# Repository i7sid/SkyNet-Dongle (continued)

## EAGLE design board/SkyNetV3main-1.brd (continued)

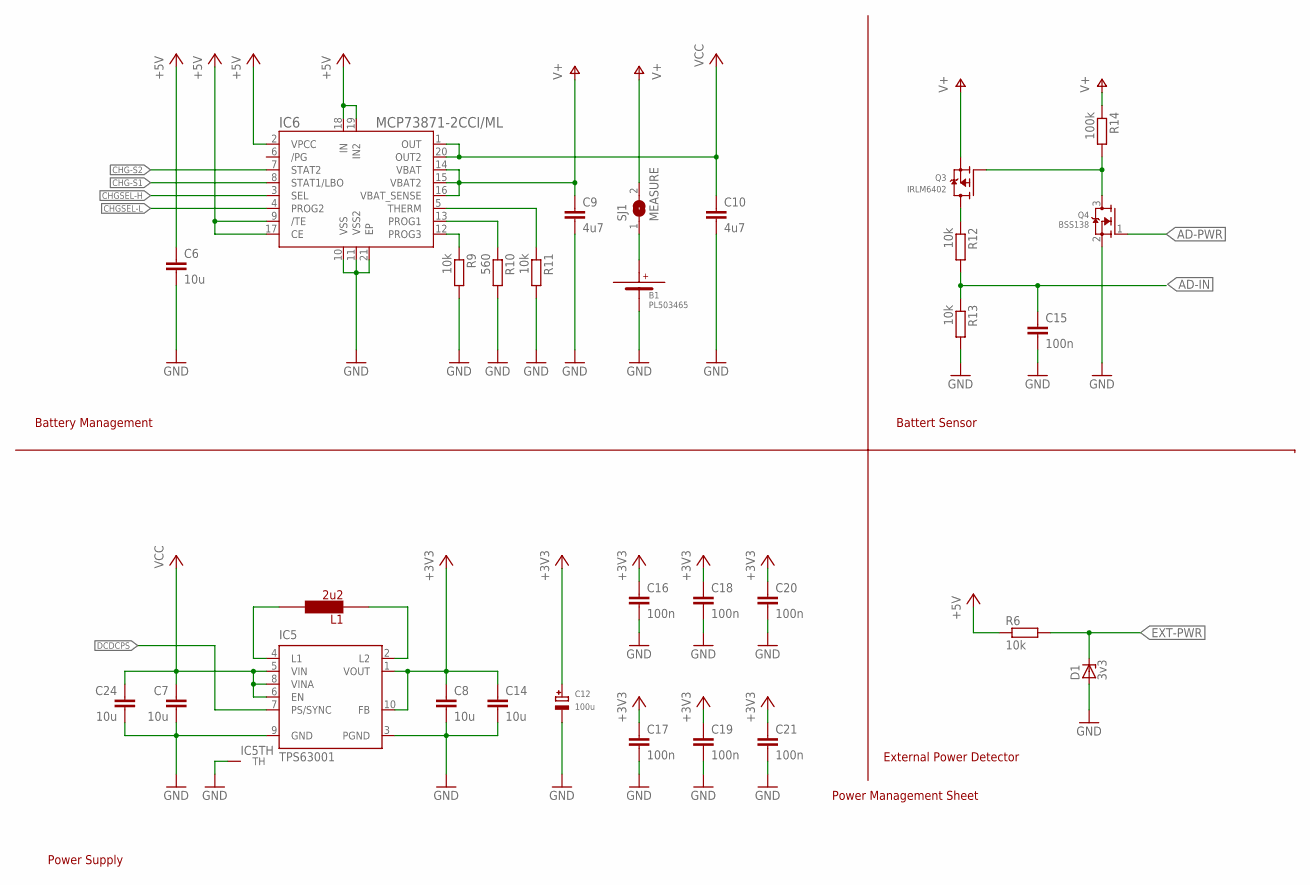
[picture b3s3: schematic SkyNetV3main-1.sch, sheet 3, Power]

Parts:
B1: PL503465
C6, C7, C8, C14, C24: 10u; C1206K
C9, C10: 4u7; C1206K
C12: 100u; EIA6032-28/C-W
C15, C16, C17, C18, C19, C20, C21: 100n; C0603
D1: 3v3; SOT23
IC5: TPS63001; DRC-S-PVSON-N10
IC6: MCP73871-2CCI/ML; QFN20-4X4
L1: 2u2; LPS4012
Q3: IRLM6402; SOT23-WIDE
Q4: BSS138; SOT23-WIDE
R6, R9, R11, R12, R13: 10k; R0603
R10: 560; R0603
R14: 100k; R0603
SJ1: MEASURE; SJ

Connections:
+3V3: C8.1, C12.+, C14.1, C16.1, C17.1, C18.1, C19.1, C20.1, C21.1, IC5.1 (VOUT), IC5.10 (FB); also elsewhere on the board
+5V: C6.1, IC6.2 (VPCC), IC6.9 (/TE), IC6.17 (CE), IC6.18 (IN), IC6.19 (IN2), R6.1; also elsewhere on the board
AD-IN: C15.1, R12.2, R13.1; also elsewhere on the board
AD-PWR: Q4.1 (G); also elsewhere on the board
AD-PWR-FET: Q3.1 (G), Q4.3 (D), R14.2
AD-PWR-FET2: Q3.3 (D), R12.1
CHG-S1: IC6.8 (STAT1/LBO); also elsewhere on the board
CHG-S2: IC6.7 (STAT2); also elsewhere on the board
CHGSEL-H: IC6.3 (SEL); also elsewhere on the board
CHGSEL-L: IC6.4 (PROG2); also elsewhere on the board
DCDCPS: IC5.7 (PS/SYNC); also elsewhere on the board
EXT-PWR: D1.3 (C), R6.2; also elsewhere on the board
GND: B1.P-, C6.2, C7.2, C8.2, C9.2, C10.2, C12.-, C14.2, C15.2, C16.2, C17.2, C18.2, C19.2, C20.2, C21.2, C24.2, D1.1 (A), IC5.3 (PGND), IC5.9 (GND), IC5.TH, IC6.10 (VSS), IC6.11 (VSS2), IC6.21 (EP), Q4.2 (S), R9.2, R10.2, R11.2, R13.2; also elsewhere on the board
L1: IC5.4 (L1), L1.1
L2: IC5.2 (L2), L1.2
unnamed: B1.P+, SJ1.1
PROG1: IC6.13 (PROG1), R10.1
PROG3: IC6.12 (PROG3), R9.1
THERM: IC6.5 (THERM), R11.1
V+: C9.1, IC6.14 (VBAT), IC6.15 (VBAT2), IC6.16 (VBAT_SENSE), Q3.2 (S), R14.1, SJ1.2
VCC: C7.1, C10.1, C24.1, IC5.5 (VIN), IC5.6 (EN), IC5.8 (VINA), IC6.1 (OUT), IC6.20 (OUT2)

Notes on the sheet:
Battery Management
Power Supply
External Power Detector
Battert Sensor
Power Management Sheet

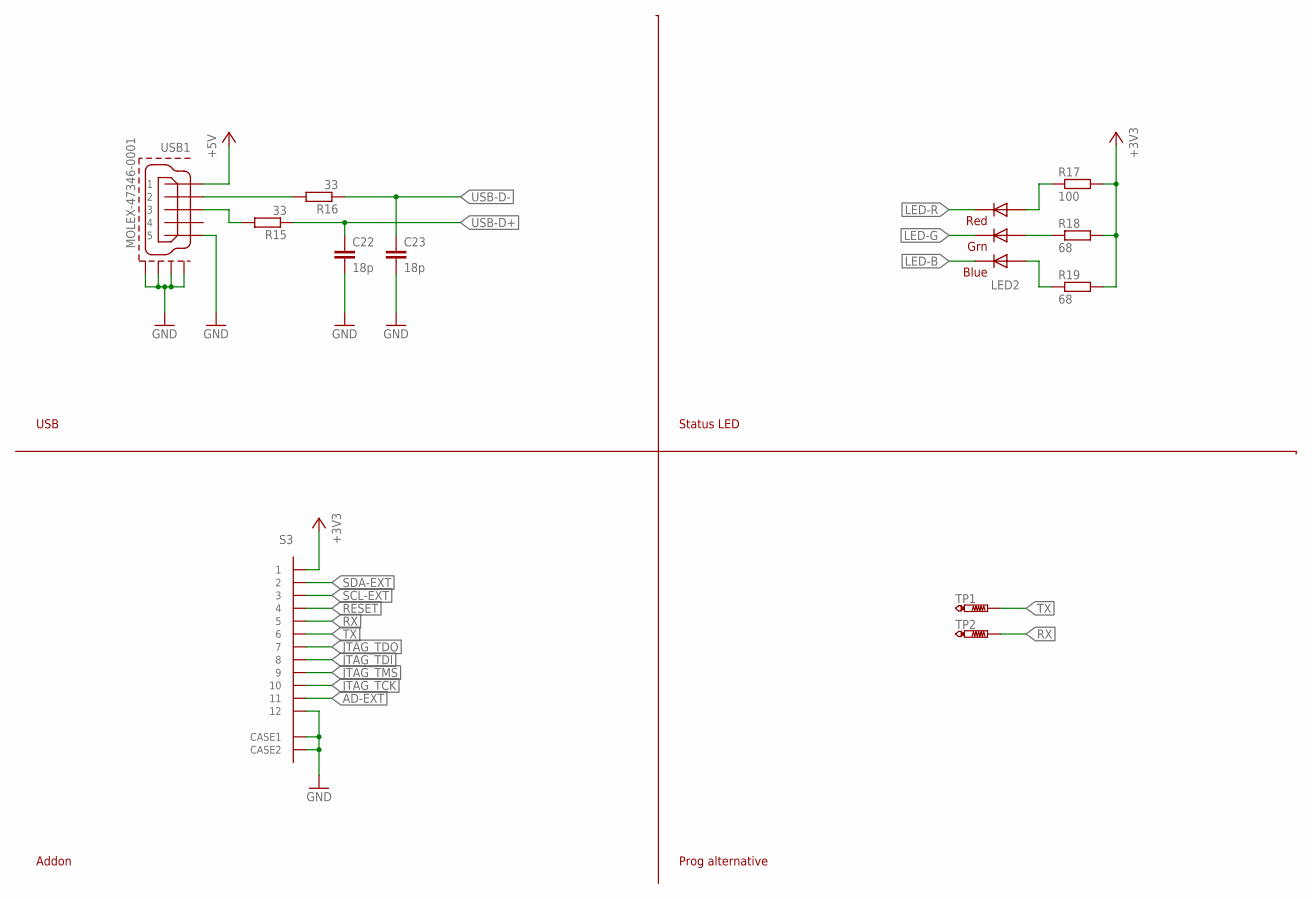
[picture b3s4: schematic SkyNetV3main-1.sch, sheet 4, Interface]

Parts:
C22, C23: 18p; C0603
LED2: RGBLED5050
R15, R16: 33; R0603
R17: 100; R0603
R18, R19: 68; R0603
S3: MOLEX-52892-1233
TP1, TP2: PTR1B1,27; B1,27
USB1: MOLEX-47346-0001; MOLEX-47364-0001

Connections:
+3V3: R17.2, R18.2, R19.2, S3.P$1 (1); also elsewhere on the board
+5V: USB1.1; also elsewhere on the board
AD-EXT: S3.P$11 (11); also elsewhere on the board
GND: C22.2, C23.2, S3.P$12 (12), S3.P$GND1 (CASE1), S3.P$GND2 (CASE2), USB1.5, USB1.GND1, USB1.GND2, USB1.GND3, USB1.GND4; also elsewhere on the board
JTAG_TCK: S3.P$10 (10); also elsewhere on the board
JTAG_TDI: S3.P$8 (8); also elsewhere on the board
JTAG_TDO: S3.P$7 (7); also elsewhere on the board
JTAG_TMS: S3.P$9 (9); also elsewhere on the board
LED-B: LED2.4 (BLUE_C); also elsewhere on the board
LED-B-R: LED2.3 (BLUE_A), R19.1
LED-G: LED2.6 (GREEN_C); also elsewhere on the board
LED-G-R: LED2.1 (GREEN_A), R18.1
LED-R: LED2.5 (RED_C); also elsewhere on the board
LED-R-R: LED2.2 (RED_A), R17.1
RESET: S3.P$4 (4); also elsewhere on the board
RX: S3.P$5 (5), TP2.TP; also elsewhere on the board
SCL-EXT: S3.P$3 (3); also elsewhere on the board
SDA-EXT: S3.P$2 (2); also elsewhere on the board
TX: S3.P$6 (6), TP1.TP; also elsewhere on the board
USB-CABLE-D+: R15.2, USB1.3; also elsewhere on the board
USB-CABLE-D-: R16.2, USB1.2
USB-D+: C22.1, R15.1; also elsewhere on the board
USB-D-: C23.1, R16.1; also elsewhere on the board

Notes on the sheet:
USB
Status LED
Prog alternative
Addon

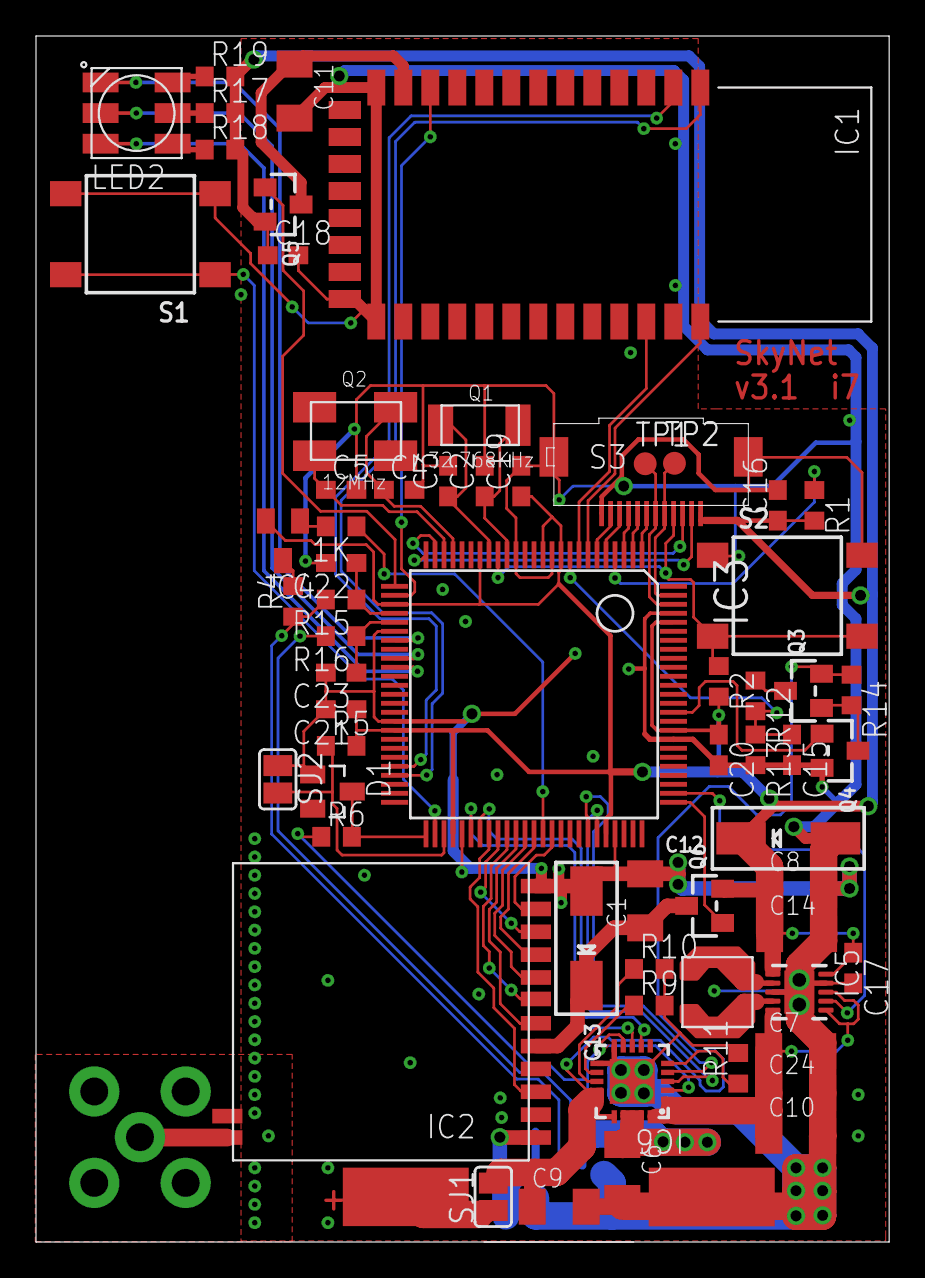
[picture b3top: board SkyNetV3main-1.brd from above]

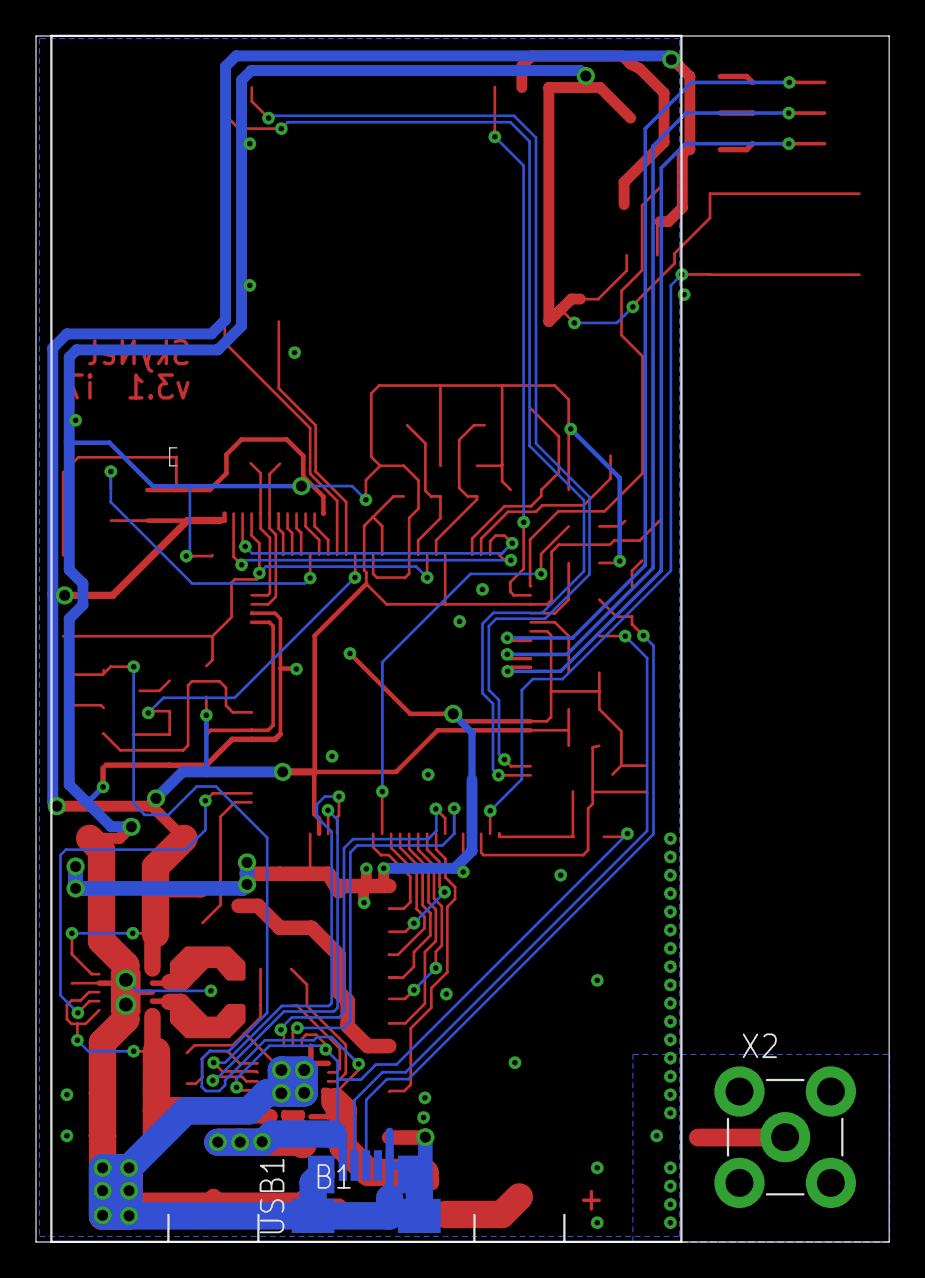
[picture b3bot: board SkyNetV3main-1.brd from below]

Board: 2 copper layers, 47.4 x 67.0 mm, 66 parts (3 on the bottom side), 68 nets.

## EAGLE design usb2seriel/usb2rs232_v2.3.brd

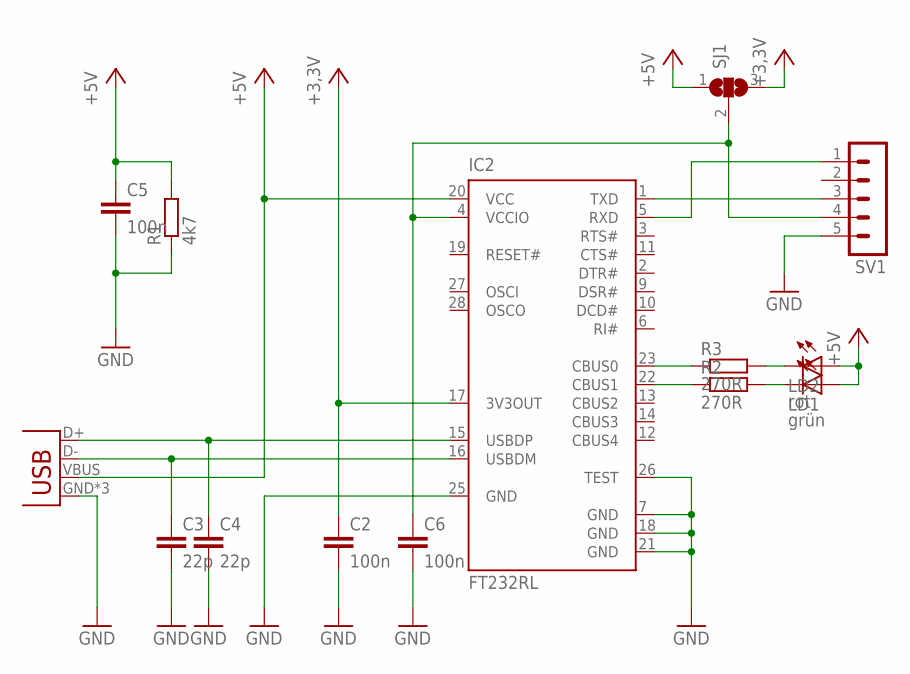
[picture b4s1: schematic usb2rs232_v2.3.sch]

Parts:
C2, C5, C6: 100n; C0603
C3, C4: 22p; C0603
IC2: FT232RL; SSOP28
JP2: USB-MICROB
LD1: grün; CHIP-LED0603
LD2: rot; CHIP-LED0603
R1: 4k7; R0603
R2, R3: 270R; R0603
SJ1: SJ2W; SJ_2
SV1: MA05-1

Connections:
+3,3V: C2.1, IC2.17 (3V3OUT), SJ1.3
+5V: C5.1, IC2.20 (VCC), JP2.VBUS, LD1.A, LD2.A, R1.2, SJ1.1
GND: C2.2, C3.2, C4.2, C5.2, C6.2, IC2.7 (GND), IC2.18 (GND), IC2.21 (GND), IC2.25 (GND), IC2.26 (TEST), JP2.GND, JP2.MT1 (GND), JP2.MT2 (GND), R1.1, SV1.5
unnamed: IC2.23 (CBUS0), R3.1
unnamed: IC2.22 (CBUS1), R2.1
unnamed: C4.1, IC2.15 (USBDP), JP2.D+
unnamed: C3.1, IC2.16 (USBDM), JP2.D-
unnamed: C6.1, IC2.4 (VCCIO), SJ1.2, SV1.4
unnamed: LD1.C, R2.2
unnamed: LD2.C, R3.2
unnamed: IC2.5 (RXD), SV1.1
unnamed: IC2.1 (TXD), SV1.3

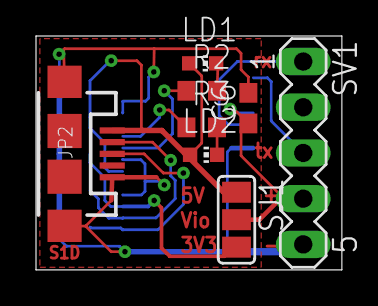
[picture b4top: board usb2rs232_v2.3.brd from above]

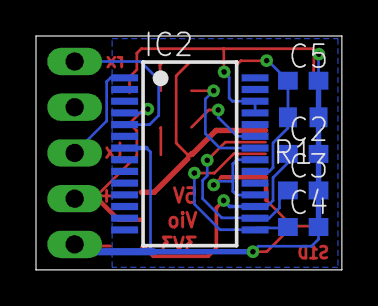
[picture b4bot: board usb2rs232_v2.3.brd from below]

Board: 2 copper layers, 17.0 x 13.0 mm, 14 parts (6 on the bottom side), 12 nets.

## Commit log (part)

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2014-05-26 basic directory structure
2014-05-26 initial commit (schematics)
    + first version of README.md
    + first sketch of schematics
    TODO on schematics:
    + power supply, charging and battery interfacing
2014-06-10 further schematics development; layout started
2014-06-10 further layout, got stuck somewhere...
2014-06-10 board further
2014-06-10 added ground planes
2014-06-11 layout optimizations, tStop corrected
2014-06-13 new layout
2014-06-15 another layout try, looks much better now
2014-06-16 layout improvements
2014-06-16 corrected USB connector in layout+schematics
2014-06-16 usb2seriel adapter for debugging and firmware uploading
2014-06-17 corrected some distance problems and missing VALUEs
2014-07-15 initial firmware commit
    no "read to run" version
2014-07-31 further firmware
2014-08-15 some further firmware work
    + RF working
    + bluetooth basically working
    TODO:
    - switch on / off
    - ...
2014-08-15 bluetooth pairing possible
2014-08-17 sleep basically works; basic RF transceiving works
2014-08-18 layout & schematic fixes
    + layout: better ground flow
    + layout: more space for single parts
    + layout: marked GND on battery
    + layout: marked pinouts
    + schematics: fixed USB-connect->USB-plus connection
2014-08-18 prepared firmware for flashing via USB
2014-09-07 firmware cleanups and TODOs, USB bootloader added
    + added 2 projects from Code Red Technologies to support USB bootloading
2014-09-16 variable packets with 4096B - that must be enough!
2014-09-16 some cleanups
2014-09-21 bluetooth is_connected stuff, event handling for packets
2014-10-11 board: connected PS/SYNC of buck boost converter
2014-10-14 Connected PS/SYNC of DC/DC
2014-10-14 some minor firmware changes
2014-10-14 minor firmware things
2014-11-07 Schematic revised. TODO Radio remains
2014-11-13 Schematic revised
2014-11-14 psu done
2014-11-15 firmware: Check "is BT connected" via GPIO
    behaviour was: enable AT mode, ask, disable AT mode
    (was very unstable!)
2014-11-17 cpu moved
2014-11-21 pre-molex-connector
2014-11-24 routing done
2014-11-24 cleanup after routing
2014-11-27 new connector
2014-12-01 case added
2015-01-13 added support for usb pocket
2015-01-13 position adjustments
2015-01-13 added todos
2015-01-16 first try of breakout board
2015-01-20 breakout board now one-sided
2015-01-22 adapted firmware to new board
2015-01-22 net names corrected for led
2015-01-29 next iteration
2015-01-29 reduzed button radius
2015-02-02 breakout board added header
2015-02-02 slightly adjusted to new board, no bootloader
    currently the memory map is configured such that
    no usb bootloader should be installed
    (for development and testing purposes)
2015-02-02 added doc (removed vom gitignore)
2015-02-07 some debugging stuff added (testing current consumption)
2015-02-09 added mounting holes
2015-03-04 debug stuff added
2015-04-01 mini dongle added
2015-04-07 improved placement
2015-04-09 added dcdc
2015-04-14 almost done
2015-04-15 mitten drin
2015-04-16 done
2015-04-27 first version of basestation firmware
2015-04-27 new files for basestation firmware
2015-04-27 fixed winddirection overflow
2015-04-29 implemented mutex and synchronisation of adc access
2015-05-07 using buffered event queue now
2015-05-07 fixed gpio interrupt
2015-06-11 bugfixing, cleanup, gpiointerrupt, doku, gpsmodul
2015-06-11 deleted old files
2015-06-24 ported to board version 3.1
2015-07-10 Some funktionalities of the Communikation Protokoll and bug fixing
2015-07-10 some more fixing
2015-07-26 more features of communication protokoll
2015-10-23 first successfull usb cdc test; LED: adjusted to single
2015-10-25 adjusted gitignore to ignore eclipse .metadata dir
2015-10-25 usb cdc driver interface, event added
2015-10-25 forgot return statement
2015-11-09 adjusted led
2015-11-10 basestation rewrite started (removed old completely)
    + usb message
    + usb host application started
2015-11-10 updated source documentation
2015-11-11 usb messages work now from uC to Host
2015-11-11 usb works in both directions; better events
2015-11-13 usb host improved, minor cleanups
2015-11-13 cleaned up, added debug scenarios
2015-11-13 further cleanups (code: warnings, more bluetooth stuff)
2015-11-17 forgotten free added; skynet<->usb bidirectional
2015-11-18 usb improved
2015-12-03 added reference to test repo for bootloader
2015-12-04 bootloader working again
2015-12-04 added debug config for version with bootloader
    + removed old launch configurations
2015-12-04 host application improved; some debug adjustments
2015-12-04 minor optical improvement in host
2015-12-04 again minor optical in host
2015-12-04 host: added method to reset device
2015-12-04 bootloader added (no git submodules; including binary build)
2015-12-04 adjusted README to new bootloader
2015-12-05 some compass tests
2015-12-06 windvane works
2015-12-06 wind cups added
2015-12-06 some code cleanups
2015-12-06 updated doxygen build
2016-01-06 gps basically works
2016-01-29 compass works basically
2016-01-29 compass: cleaned up code
2016-02-01 bootloader: generate checksum; load user prog only if checksum valid
2016-02-02 first data structures for mac
2016-02-04 small fix, test added
2016-02-05 crc integrated
2016-02-05 adjusted some mac stuff to board
2016-02-05 added source to crc16 function
2016-02-08 added bash script to create tap device
2016-03-15 mac further
2016-03-15 mac packet assembly further
2016-04-05 before lpcxpresso update
2016-04-06 after lpcxpresso ide update
2016-04-06 some cleanup
2016-04-06 minor cleanups
2016-04-06 fixed usb not reconnecting, minor cleanup
2016-04-06 small fixes/workarounds, TAP testing
2016-04-08 mac data frame: unpack method; host: some stuff
2016-04-08 host: tap->usb further
2016-04-08 changed host to work an mac layer
2016-04-08 changed usb-host to makefile project, no need for eclipse/LPCXpresso
2016-04-08 removed binary
2016-04-08 host: error handling improved
2016-04-08 improved cdc handling: larger packets possible (via hack)
2016-04-08 removed debug return in host
2016-04-08 fixed some host issues
2016-04-09 fixed bug with fstream in host app
2016-04-09 added sysctl call to setup-tap-script
    avoid problems with reverse packet filter
2016-04-09 host: improved setup script
2016-04-12 host debug: dest mac addr always broadcast
2016-04-12 host: some further debug
2016-04-12 host: further debug (tap: no packet info)
2016-04-12 transmit ether_type in src_address
2016-04-12 fixed bug in mac addresses
2016-04-12 arp works via ether_type hack, so do not disable on setup
2016-04-13 host debug further
2016-04-13 dbg host: added some bytes at end that may be destroyed
2016-04-13 dbg host: try to correct bug in previous workaround
2016-04-13 host: decreased overhead
2016-04-13 removed backup file that was added by chance
2016-04-13 some firmware changes for cdc and tunneling
2016-04-14 todo marker
2016-04-14 improved usb timing
2016-04-14 watchdog added
2016-04-14 some adjustments for base
2016-04-19 nv storage, etc.
2016-04-19 firmware binary for demo added
2016-04-19 usb timing parameter adjusted
2016-04-19 host: removed debug outputs
2016-04-19 some host debug
2016-04-19 some debug for large packets
2016-04-19 debug further
2016-04-19 some timing tests on host side
2016-04-19 bug with queue fixed
2016-04-20 host debug
2016-04-20 host: reopen tty automatically
2016-04-20 host: bug in memory allocation fixed
2016-04-20 some improvements in usb cdc handling
2016-04-20 added mtu to setup-tap.sh
2016-04-28 first try for extheaders in mac
2016-04-28 fixed malloc size bug in extheader unpack
2016-04-28 base station basically sends
2016-04-29 dongle cmd added, some further extheaders, sync for events
2016-04-30 compass calibration works
2016-05-01 some refactoring of host
2016-05-01 some cleanup, ncurses added to makefile
2016-05-01 ncurses further
2016-05-01 menu basically works
2016-05-02 some gui working
2016-05-02 nearly no linux/* headers
2016-05-02 added compile time option to disable tap
2016-05-02 tried to remove further ethernet dependencies for NO_TAP
2016-05-03 some mysql stuff for host app
2016-05-03 main.c for basestation fix
2016-05-03 first web models (using doctrine2)
2016-05-04 removed bug in radio TX
    Hooray!
    + many gui features...
2016-05-06 tests for base station
2016-05-06 NO_DB for host app
2016-05-06 NO_DB fix further
2016-05-06 NO_TAP fixed
2016-05-06 applied si4463 patch, minor fixes
2016-05-07 found problem (was crc) + some debug stuff
2016-05-07 stil some problems
2016-05-07 possible workaround for weird packet handler bug
    clear tx fifo after TX by manually writing 0x0
2016-05-07 small radio improvement
2016-05-07 windspeed measurement improved
2016-05-07 small host fixes
2016-05-07 firmware: added -Werror, warnings=errors
    + adjusted code to compile
2016-05-07 adjusted radio_cts_timeout
2016-05-07 better seed for PRNG
2016-05-07 base: generate random mac if none set
2016-05-07 changed wind dir to compensated
2016-05-07 CSMA: CCA adjusted
2016-05-10 gui compiling bug fixed
    + some preparations for resizable GUI
2016-05-10 send-ack-method added; volatile configuration
2016-05-11 added compile configurations for base; some code cleanup
2016-05-11 minor code cleanup; added broadcast reception
2016-05-11 write sensor data to text file (for sure)
2016-05-11 fixed bug in wind speed: got never null
2016-05-12 radio pa level config msg; fixed host compile bug
2016-05-12 base: fixed bug in auto-mac routine
2016-05-14 php: simple script for db output added
2016-05-17 fixed missing free() in firmware
2016-05-17 some gui improvements; added payload RX terminating null byte
2016-05-17 db model: changed entity value to string
2016-05-17 php export: positions and mean of positions
2016-05-17 adjusted .gitignore of usb-host
2016-05-19 host: start/stop measurement
2016-05-19 compatibility for cygwin improved
2016-05-19 fix prev commit
2016-06-10 some (preperation) tries for ACKs; SEND EACH PACKET 3 TIMES
2016-06-16 fixed bug in compass calibration; send winddir raw
2016-06-16 gui: added function to stop calibration manually
2016-06-21 rf power test
2016-06-21 basic data structure for measurement
2016-06-21 host: better incoming data representation and presentation
2016-06-21 added better output framework, basic station output json
2016-06-22 basic wind drawing in map (QGIS via GeoJSON)
2016-06-22 added new csv output module
2016-06-23 DB as new output handler
2016-06-23 host: averaging (intuitive not-optimized algorithm)
2016-06-24 added basic multihop functionality
2016-06-24 malloc and free counter output
2016-06-30 fixed some retransmission issues; added basic multihop (ttl=2)
2016-07-02 removed debug (lead to bug)
2016-07-07 test lower bitrate
2016-07-09 added compatibility for windows host
2016-07-13 fixed little bug in windspeed
2016-07-13 host: raw dir to csv output
2016-07-13 windspeed: added alternate speed measurement
2016-07-18 added usb type for simple range tests
2016-08-01 UART between base and feather works
2016-08-03 base: dfx further
2016-08-03 base with feather: works basically
    problem: multiple received packets are recognized multiple times
2016-08-05 send base to feather even if gps fix missing
2016-08-09 history in basestation
2016-08-11 base: basic CCA, watchdog
2016-09-05 feather: fixed mac bug, mac in library; multihop
2016-09-05 ide internal stuff
2016-09-05 host: first try to implement updraft detection
2016-09-05 host Makefile: TODO target
2016-09-07 host: thermal further
2016-09-07 added fifo output
2016-09-07 host: activated fifo in main
2016-09-08 fixed some fifo issues, fixed which data is transmitted
2016-09-20 environment for analysis added
2016-09-21 rangetest: rx works, some further adjustments
2016-09-22 udev rules file added
2016-09-22 fixed WDT bug in rangetest TX feather
2016-09-23 added rangetest data from 2016/09/09
2016-10-13 webapp added
2016-10-21 model before vecetor based
2016-10-21 model changed to use vector updrafts
2016-10-31 analysis environment updates
2016-10-31 some older php scripts (possibly useful)
